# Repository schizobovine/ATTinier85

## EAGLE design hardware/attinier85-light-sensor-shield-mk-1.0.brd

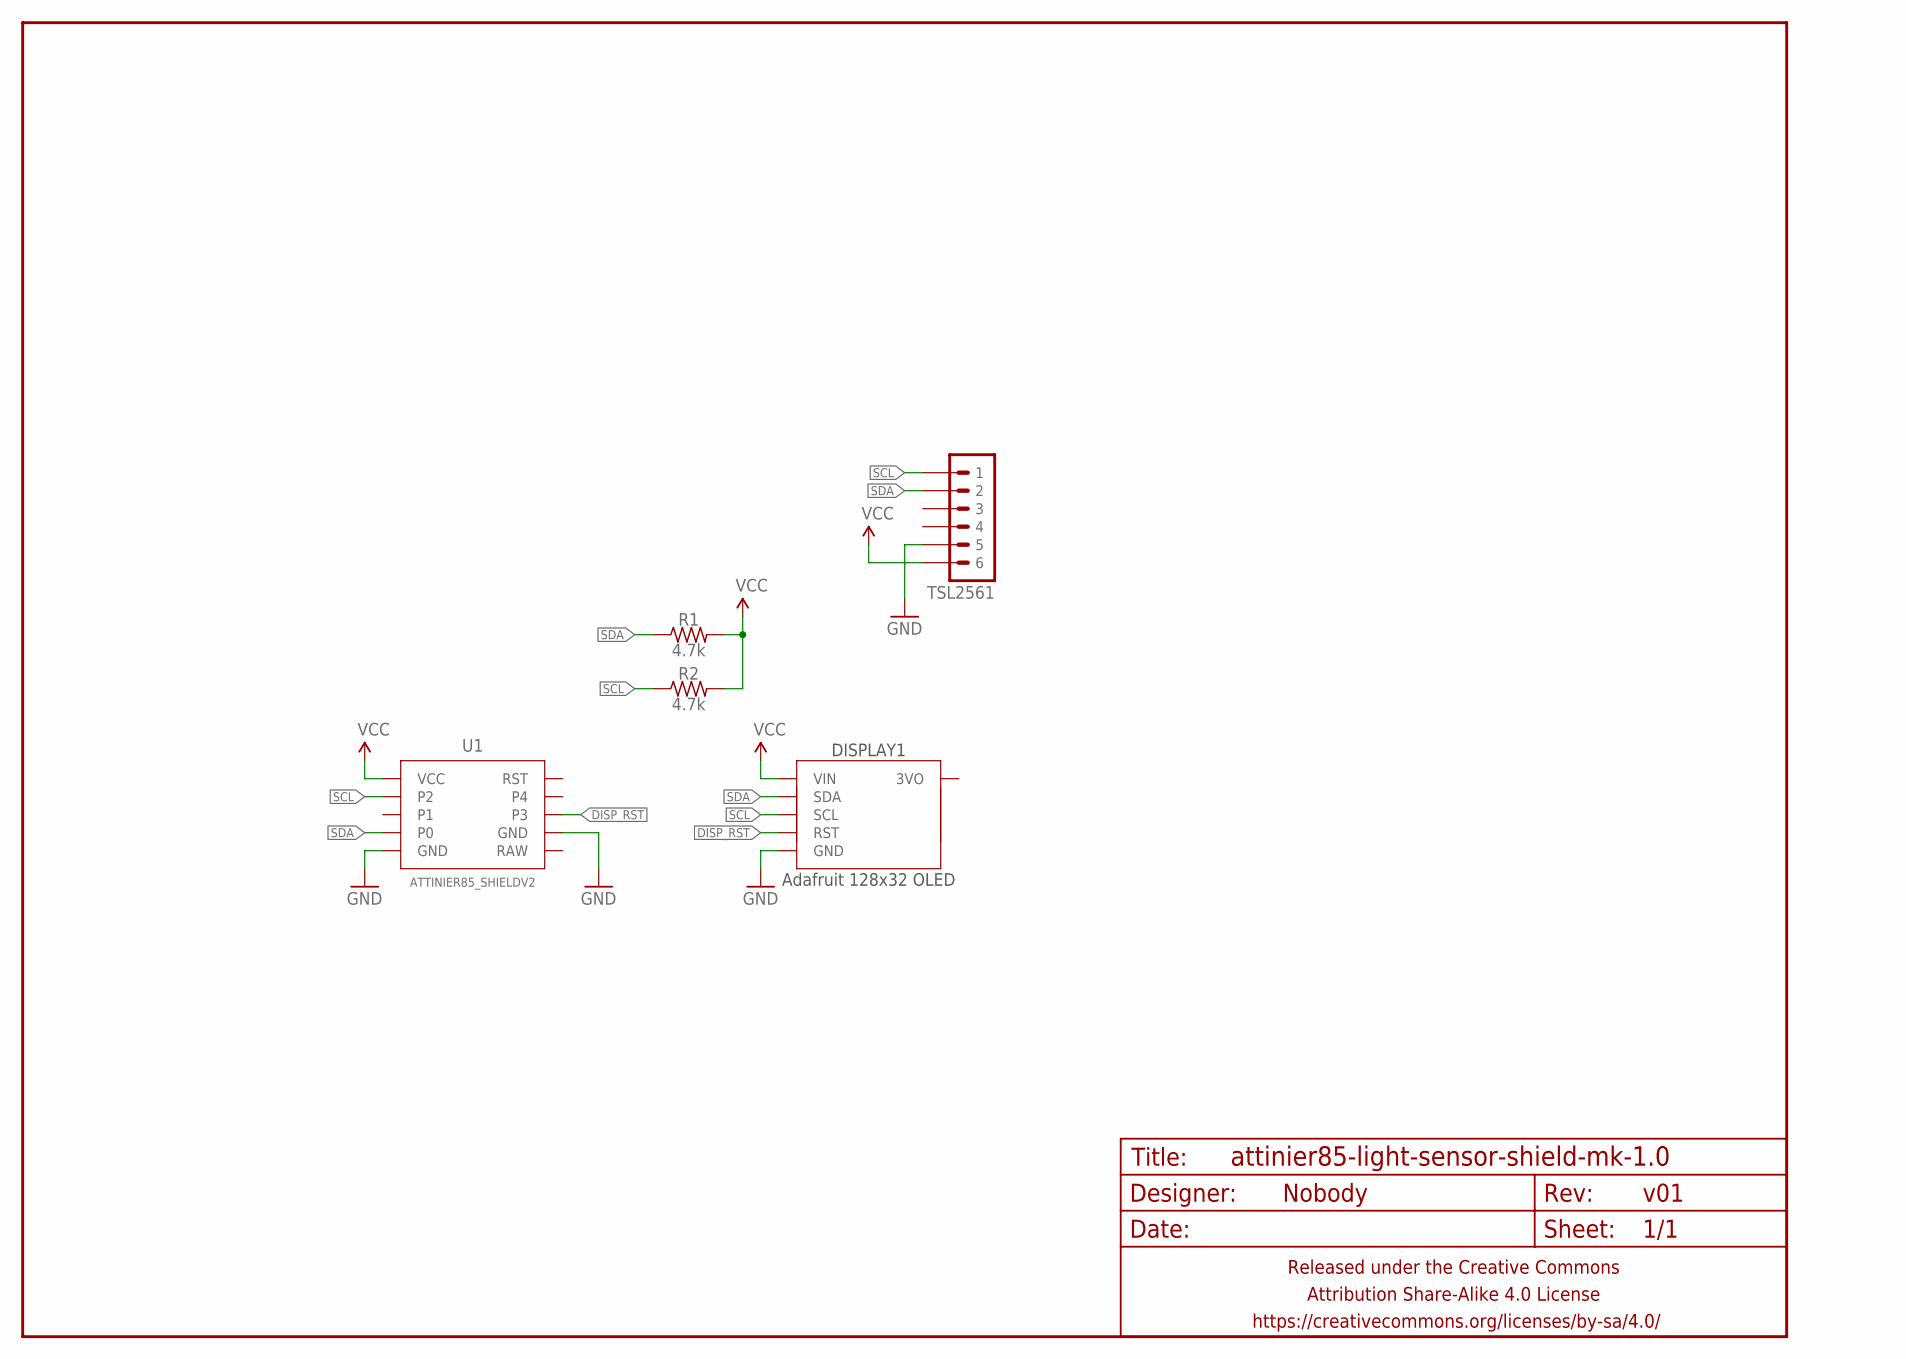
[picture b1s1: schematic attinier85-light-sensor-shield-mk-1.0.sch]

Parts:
DISPLAY1: Adafruit 128x32 OLED; ADAFRUIT_128X32_OLED_I2C_CLOSER_NOHOLES
FRAME1: FRAME-LETTERNO_PACKAGE; DUMMY
R1, R2: 4.7k; RESISTOR-AXIAL-PTH-7.62MM
TSL2561: M06CLOSER; 1X06_CLOSER
U1: ATTINIER85_SHIELDV2; ATTINIER85_SHIELD_V2

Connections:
DISP_RST: DISPLAY1.RST, U1.3
GND: DISPLAY1.GND, TSL2561.5, U1.GND@1 (GND), U1.GND@2 (GND)
SCL: DISPLAY1.SCL, R2.P$1 (1), TSL2561.1, U1.2
SDA: DISPLAY1.SDA, R1.P$1 (1), TSL2561.2, U1.0
VCC: DISPLAY1.VIN, R1.P$2 (2), R2.P$2 (2), TSL2561.6, U1.VCC

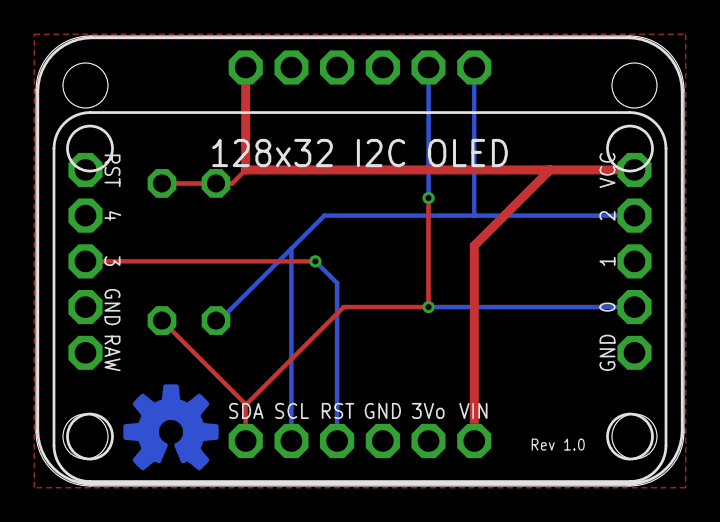
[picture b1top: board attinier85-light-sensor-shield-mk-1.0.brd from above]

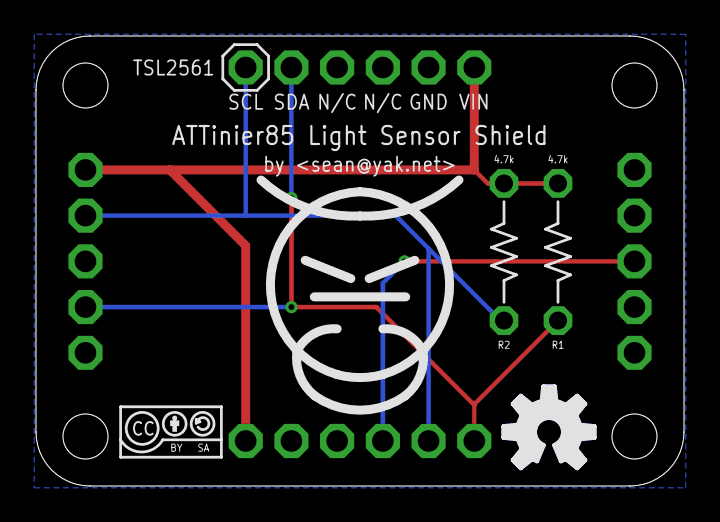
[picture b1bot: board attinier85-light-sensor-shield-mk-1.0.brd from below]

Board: 2 copper layers, 36.0 x 25.0 mm, 9 parts (6 on the bottom side), 5 nets.

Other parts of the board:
U$1: COW
U$2: CC-BY-SA-4.0-NO-URL
U$3: OSHWLOGO_TOP_0.2

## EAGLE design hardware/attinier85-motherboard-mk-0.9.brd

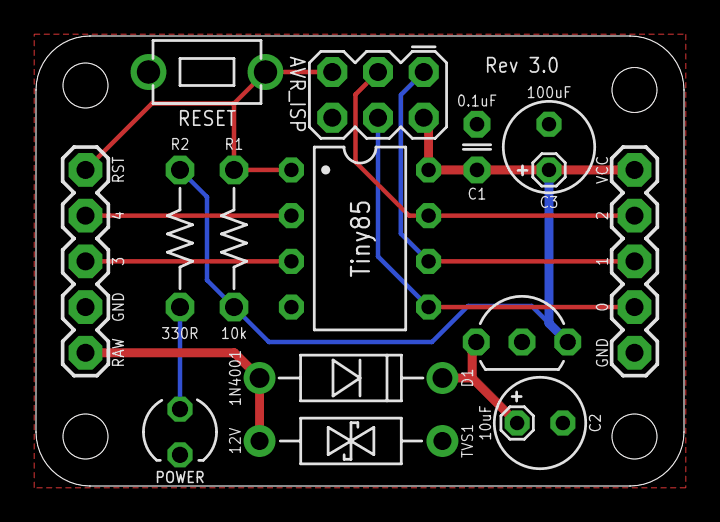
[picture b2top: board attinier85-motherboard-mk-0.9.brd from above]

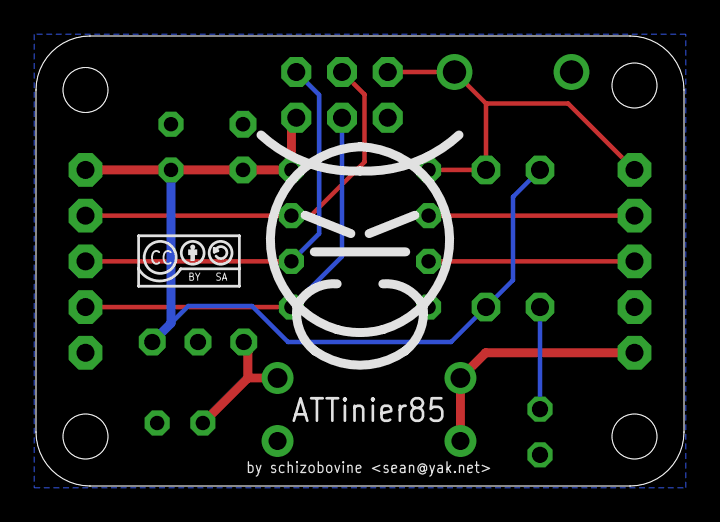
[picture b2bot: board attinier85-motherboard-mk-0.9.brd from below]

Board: 2 copper layers, 36.0 x 25.0 mm, 16 parts (2 on the bottom side), 11 nets.

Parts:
AVR_ISP: AVR_SPI_PRG_6PTH; 2X3
C1: 0.1uF; C025-024X044
C2: 10uF; E2,5-5
C3: 100uF; E2,5-5
D1: 1N4001; DIODE-10.16MM
IC1: Tiny85; DIP08
IC2: LM2931; TO-92-AMMO
JP1, JP2: M05PTH; 1X05
POWER: LED3MM-LESS; LED3MM-LESSSILK
R1: 10k; RESISTOR-AXIAL-PTH-7.62MM
R2: 330R; RESISTOR-AXIAL-PTH-7.62MM
RESET: DTS-6MM; DTS-3-SMALL-PADS
TVS1: 12V; DO-41-TVS
U$1: CC-BY-SA-4.0NO-URL; CC-BY-SA-4.0-NO-URL
U$2: COW

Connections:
D3: IC1.2, JP1.2
D4: IC1.3, JP1.3
GND: AVR_ISP.6, C1.2, C2.-, C3.-, IC1.4, IC2.2, JP1.4, JP2.1, POWER.K, RESET.1, TVS1.P$2
MISO: AVR_ISP.1, IC1.6, JP2.3
MOSI/SDA: AVR_ISP.4, IC1.5, JP2.2
unnamed: C2.+, D1.C, IC2.1
unnamed: POWER.A, R2.P$2
RAW: D1.A, JP1.5, TVS1.P$1
RST: AVR_ISP.5, IC1.1, JP1.1, R1.P$1, RESET.2
SCK/SCL: AVR_ISP.3, IC1.7, JP2.4
VCC: AVR_ISP.2, C1.1, C3.+, IC1.8, IC2.3, JP2.5, R1.P$2, R2.P$1

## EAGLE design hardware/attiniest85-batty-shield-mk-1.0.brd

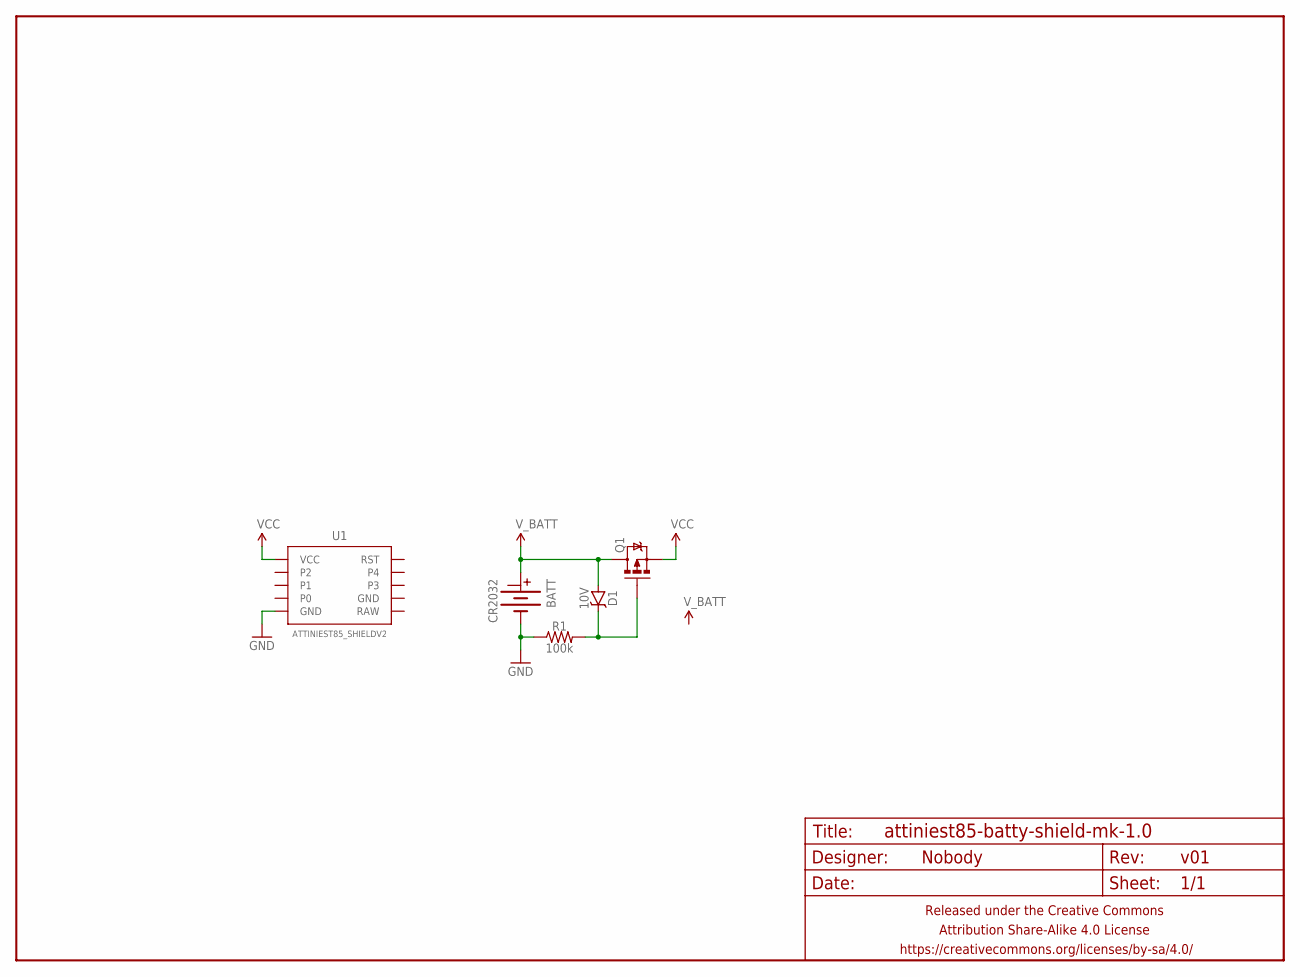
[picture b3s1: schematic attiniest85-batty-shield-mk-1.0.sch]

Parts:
BATT: CR2032; BATTCON_20MM_MINE
D1: 10V; DIODE-ZENNER-7.62MM
FRAME1: FRAME-LETTERNO_PACKAGE; DUMMY
Q1: MOSFET-PCHANNELTO-92-INLINE-DGS; TO-92-AMMO
R1: 100k; RESISTOR-AXIAL-PTH-7.62MM
U1: ATTINIEST85_SHIELDV2; ATTINIEST85_SHIELD_V2

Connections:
GND: BATT.BOTTOM (-), R1.P$1 (1), U1.GND@2 (GND)
unnamed: D1.K (C), Q1.2 (G), R1.P$2 (2)
VCC: Q1.3 (S), U1.VCC
V_BATT: BATT.TOP@1 (+), D1.A, Q1.1 (D)

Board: 2 copper layers, 6 parts (0 on the bottom side), 4 nets, no tracks yet.

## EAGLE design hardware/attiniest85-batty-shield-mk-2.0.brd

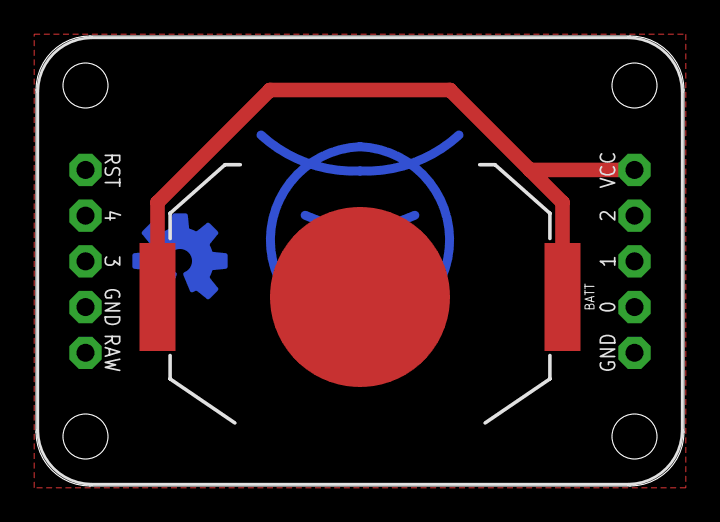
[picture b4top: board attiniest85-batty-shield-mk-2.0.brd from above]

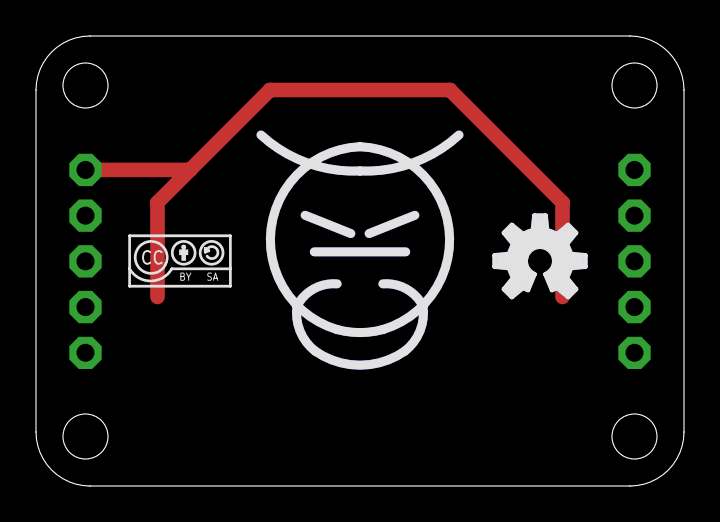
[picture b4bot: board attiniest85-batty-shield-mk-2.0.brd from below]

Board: 2 copper layers, 36.0 x 25.0 mm, 6 parts (3 on the bottom side), 2 nets.

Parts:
BATT: CR2032; BATTCON_20MM_MINE
FRAME1: DUMMY
U1: ATTINIEST85_SHIELDV2; ATTINIEST85_SHIELD_V2
U$3: CC-BY-SA-4.0-NO-URL
U$4: OSHWLOGO_TOP_0.2
U$6: COW_METAL

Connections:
GND: BATT.BOTTOM, U1.GND@2
VCC: BATT.TOP@1, BATT.TOP@2, U1.VCC

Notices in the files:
parts and their libraries:
A_butts: Released under the Creative Commons Attribution Share-Alike 4.0 License
A_butts: https://creativecommons.org/licenses/by-sa/4.0
A_butts: Released under the Creative Commons
